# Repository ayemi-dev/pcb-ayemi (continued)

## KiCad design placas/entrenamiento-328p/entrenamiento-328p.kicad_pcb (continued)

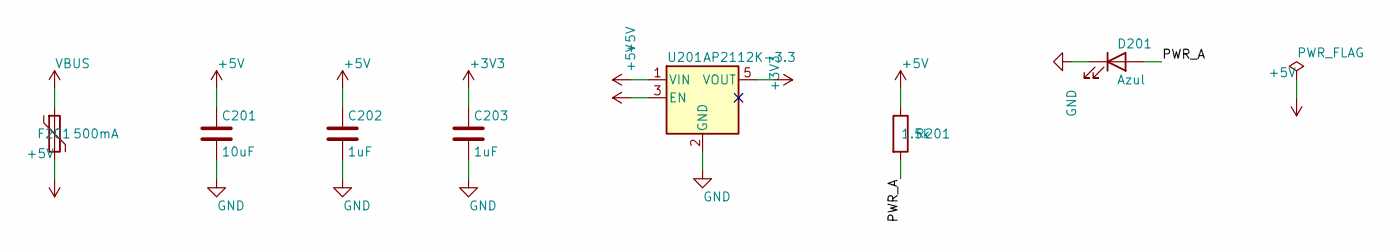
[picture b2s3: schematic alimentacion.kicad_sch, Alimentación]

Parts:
C201: 10uF; C_0603_1608Metric; LCSC C19702
C202, C203: 1uF; C_0603_1608Metric; LCSC C15849
D201: Azul; LED_0603_1608Metric; LCSC C2288
F201: 500mA; Fuse_1206_3216Metric; LCSC C163512
R201: 1.5k; R_0603_1608Metric; LCSC C22843
U201: AP2112K-3.3; SOT-23-5; LCSC C51118

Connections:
+3V3: C203.1, U201.5 (VOUT); also elsewhere on the board
+5V: C201.1, C202.1, F201.2, R201.1, U201.1 (VIN), U201.3 (EN); also elsewhere on the board
/alimentacion/PWR_A: D201.2 (A), R201.2
GND: C201.2, C202.2, C203.2, D201.1 (K), U201.2 (GND); also elsewhere on the board
VBUS: F201.1; also elsewhere on the board

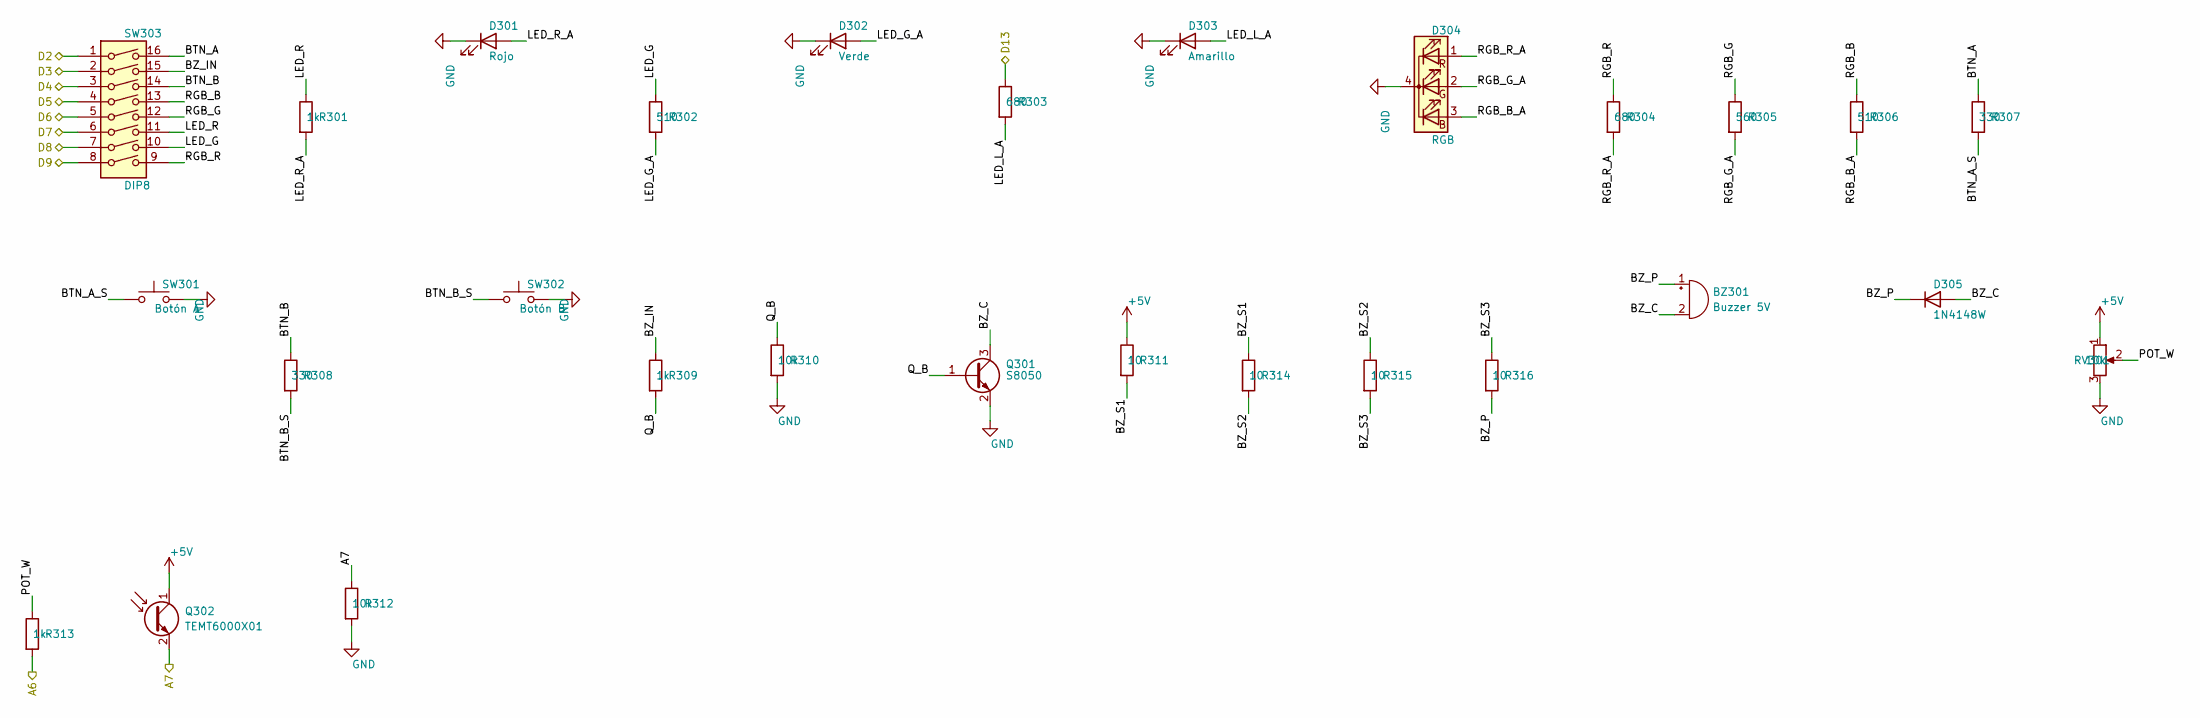
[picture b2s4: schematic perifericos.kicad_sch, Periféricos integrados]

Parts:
BZ301: Buzzer 5V; MagneticBuzzer_CUI_CMT-8504-100-SMT; LCSC C7421674
D301: Rojo; LED_0603_1608Metric; LCSC C2286
D302: Verde; LED_0603_1608Metric; LCSC C12624
D303: Amarillo; LED_0603_1608Metric; LCSC C2287
D304: RGB; LED_Avago_PLCC4_3.2x2.8mm_CW; LCSC C3647023
D305: 1N4148W; D_SOD-123; LCSC C81598
Q301: S8050; SOT-23; LCSC C2146
Q302: TEMT6000X01; LED_1206_3216Metric; LCSC C94098
R301, R309, R313: 1k; R_0603_1608Metric; LCSC C21190
R302, R306: 510; R_0603_1608Metric; LCSC C23193
R303, R304: 680; R_0603_1608Metric; LCSC C23228
R305: 560; R_0603_1608Metric; LCSC C23204
R307, R308: 330; R_0603_1608Metric; LCSC C23138
R310, R312: 10k; R_0603_1608Metric; LCSC C25804
R311, R314, R315, R316: 10; R_0603_1608Metric; LCSC C22859
RV301: 10k; Potentiometer_Alps_RK09K_Single_Vertical; LCSC C202373
SW301: Botón A; SW_Push_1TS009xxxx-xxxx-xxxx_6x6x5mm; LCSC C319409
SW302: Botón B; SW_Push_1TS009xxxx-xxxx-xxxx_6x6x5mm; LCSC C319409
SW303: DIP8; SW_DIP_SPSTx08_Slide_Omron_A6S-810x_W8.9mm_P2.54mm; LCSC C6709493

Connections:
+5V: Q302.1 (C), R311.1, RV301.1; also elsewhere on the board
/A6: R313.2; also elsewhere on the board
/A7: Q302.2 (E), R312.1; also elsewhere on the board
/D2: SW303.1; also elsewhere on the board
/D3: SW303.2; also elsewhere on the board
/D4: SW303.3; also elsewhere on the board
/D5: SW303.4; also elsewhere on the board
/D6: SW303.5; also elsewhere on the board
/D7: SW303.6; also elsewhere on the board
/D8: SW303.7; also elsewhere on the board
/D9: SW303.8; also elsewhere on the board
/D13: R303.1; also elsewhere on the board
/perifericos/BTN_A: R307.1, SW303.16
/perifericos/BTN_A_S: R307.2, SW301.1
/perifericos/BTN_B: R308.1, SW303.14
/perifericos/BTN_B_S: R308.2, SW302.1
/perifericos/BZ_C: BZ301.2 (-), D305.2 (A), Q301.3 (C)
/perifericos/BZ_IN: R309.1, SW303.15
/perifericos/BZ_P: BZ301.1 (+), D305.1 (K), R316.2
/perifericos/BZ_S1: R311.2, R314.1
/perifericos/BZ_S2: R314.2, R315.1
/perifericos/BZ_S3: R315.2, R316.1
/perifericos/LED_G: R302.1, SW303.10
/perifericos/LED_G_A: D302.2 (A), R302.2
/perifericos/LED_L_A: D303.2 (A), R303.2
/perifericos/LED_R: R301.1, SW303.11
/perifericos/LED_R_A: D301.2 (A), R301.2
/perifericos/POT_W: R313.1, RV301.2
/perifericos/Q_B: Q301.1 (B), R309.2, R310.1
/perifericos/RGB_B: R306.1, SW303.13
/perifericos/RGB_B_A: D304.3 (BA), R306.2
/perifericos/RGB_G: R305.1, SW303.12
/perifericos/RGB_G_A: D304.2 (GA), R305.2
/perifericos/RGB_R: R304.1, SW303.9
/perifericos/RGB_R_A: D304.1 (RA), R304.2
GND: D301.1 (K), D302.1 (K), D303.1 (K), D304.4 (K), Q301.2 (E), R310.2, R312.2, RV301.3, SW301.2, SW302.2; also elsewhere on the board

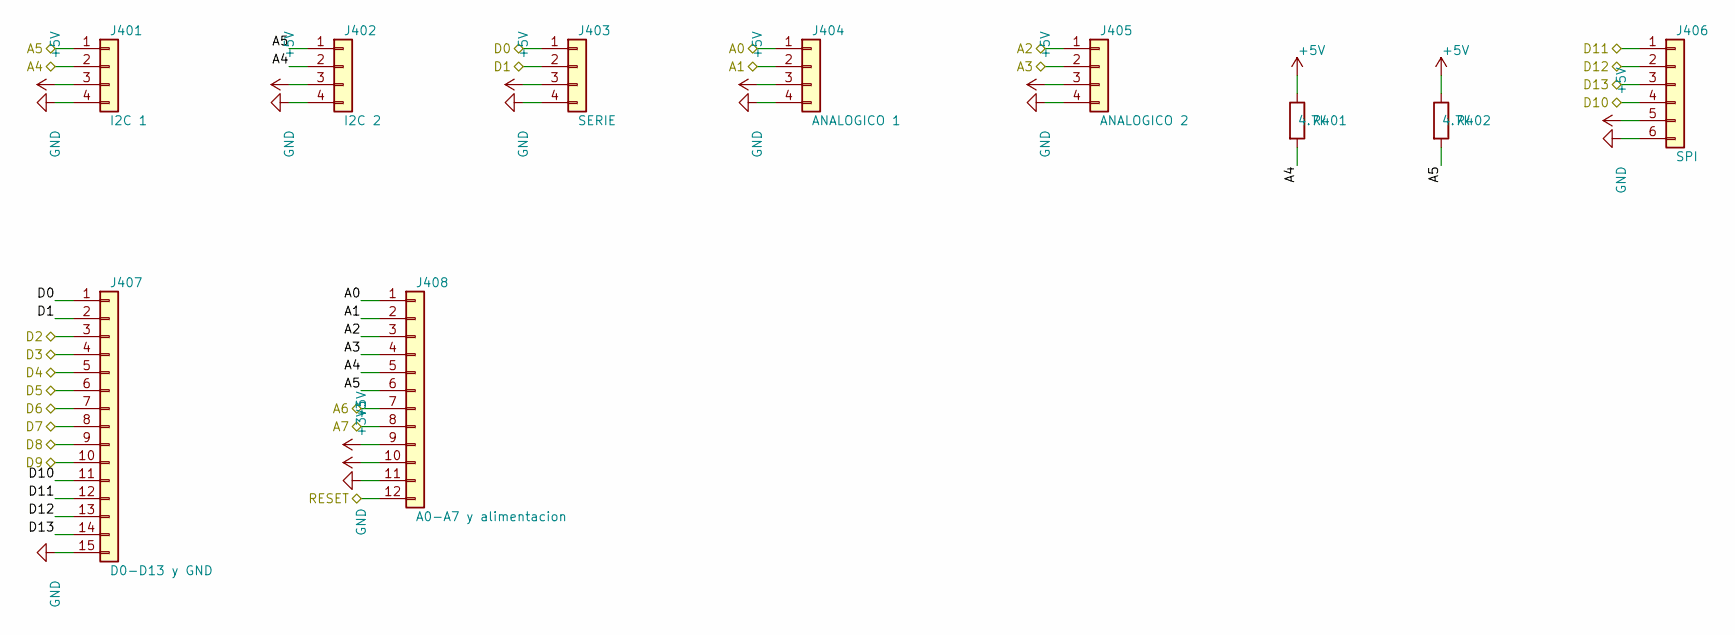
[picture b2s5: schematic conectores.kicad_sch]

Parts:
J401: I2C 1; JST_PH_S4B-PH-SM4-TB_1x04-1MP_P2.00mm_Horizontal; LCSC C265102
J402: I2C 2; JST_PH_S4B-PH-SM4-TB_1x04-1MP_P2.00mm_Horizontal; LCSC C265102
J403: SERIE; JST_PH_S4B-PH-SM4-TB_1x04-1MP_P2.00mm_Horizontal; LCSC C265102
J404: ANALOGICO 1; JST_PH_S4B-PH-SM4-TB_1x04-1MP_P2.00mm_Horizontal; LCSC C265102
J405: ANALOGICO 2; JST_PH_S4B-PH-SM4-TB_1x04-1MP_P2.00mm_Horizontal; LCSC C265102
J406: SPI; PinHeader_1x06_P2.54mm_Vertical; LCSC C492405
J407: D0-D13 y GND; PinHeader_1x15_P2.54mm_Vertical; LCSC C22465875
J408: A0-A7 y alimentacion; PinHeader_1x12_P2.54mm_Vertical; LCSC C2840012
R401, R402: 4.7k; R_0603_1608Metric; LCSC C23162

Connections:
+3V3: J408.10; also elsewhere on the board
+5V: J401.3, J402.3, J403.3, J404.3, J405.3, J406.5, J408.9, R401.1, R402.1; also elsewhere on the board
/A0: J404.1, J408.1; also elsewhere on the board
/A1: J404.2, J408.2; also elsewhere on the board
/A2: J405.1, J408.3; also elsewhere on the board
/A3: J405.2, J408.4; also elsewhere on the board
/A4: J401.2, J402.2, J408.5, R401.2; also elsewhere on the board
/A5: J401.1, J402.1, J408.6, R402.2; also elsewhere on the board
/A6: J408.7; also elsewhere on the board
/A7: J408.8; also elsewhere on the board
/D0: J403.1, J407.1; also elsewhere on the board
/D1: J403.2, J407.2; also elsewhere on the board
/D2: J407.3; also elsewhere on the board
/D3: J407.4; also elsewhere on the board
/D4: J407.5; also elsewhere on the board
/D5: J407.6; also elsewhere on the board
/D6: J407.7; also elsewhere on the board
/D7: J407.8; also elsewhere on the board
/D8: J407.9; also elsewhere on the board
/D9: J407.10; also elsewhere on the board
/D10: J406.4, J407.11; also elsewhere on the board
/D11: J406.1, J407.12; also elsewhere on the board
/D12: J406.2, J407.13; also elsewhere on the board
/D13: J406.3, J407.14; also elsewhere on the board
/RESET: J408.12; also elsewhere on the board
GND: J401.4, J402.4, J403.4, J404.4, J405.4, J406.6, J407.15, J408.11; also elsewhere on the board

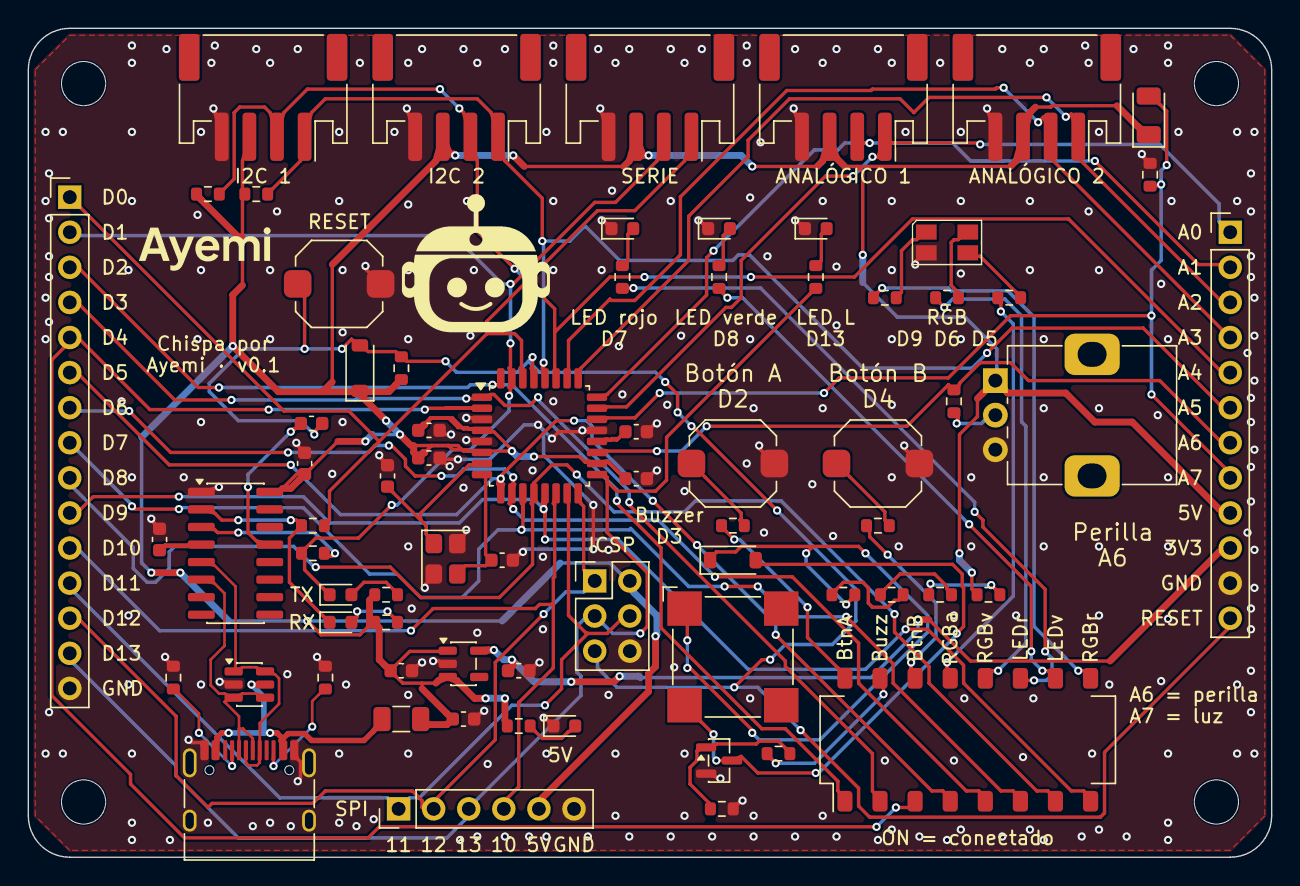
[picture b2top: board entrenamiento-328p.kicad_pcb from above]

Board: 2 copper layers, 90.0 x 60.0 mm, 75 parts (0 on the bottom side), 64 nets.

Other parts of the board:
H1, H2, H3, H4: M3; MountingHole_3.2mm_M3

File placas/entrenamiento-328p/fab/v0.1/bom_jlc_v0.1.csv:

Comment,Designator,Footprint,LCSC Part #,Clase,Alternativa
Buzzer 5V,BZ301,MagneticBuzzer_CUI_CMT-8504-100-SMT,C7421674,Extended,C530411
22pF,"C1,C2",C_0603_1608Metric,C1653,Basic,C7419421
100nF,"C3,C4,C5,C6,C101,C102,C103",C_0603_1608Metric,C14663,Basic,C91183
10uF,C201,C_0603_1608Metric,C19702,Basic,C380314
1uF,"C202,C203",C_0603_1608Metric,C15849,Basic,C106214
1N4148W,"D1,D305",D_SOD-123,C81598,Basic,C2099
C2286,"D101,D102,D301",LED_0603_1608Metric,C2286,Basic,C84263
Azul,D201,LED_0603_1608Metric,C2288,Extended,C84266
Verde,D302,LED_0603_1608Metric,C12624,Extended,C84267
Amarillo,D303,LED_0603_1608Metric,C2287,Extended,C84268
RGB,D304,LED_Avago_PLCC4_3.2x2.8mm_CW,C3647023,Extended,C601684
500mA,F201,Fuse_1206_3216Metric,C163512,Extended,C49318356
ICSP,J1,PinHeader_2x03_P2.54mm_Vertical,C65114,Extended,C53055678
USB-C,J101,USB_C_Receptacle_HRO_TYPE-C-31-M-12,C165948,Extended,C5337088
C265102,"J401,J402,J403,J404,J405",JST_PH_S4B-PH-SM4-TB_1x04-1MP_P2.00mm_Horizontal,C265102,Extended,C7429571
SPI,J406,PinHeader_1x06_P2.54mm_Vertical,C492405,Extended,C42431790
D0-D13 y GND,J407,PinHeader_1x15_P2.54mm_Vertical,C22465875,Extended,C2932704
A0-A7 y alimentacion,J408,PinHeader_1x12_P2.54mm_Vertical,C2840012,Extended,C54803345
S8050,Q301,SOT-23,C2146,Basic,C105433
TEMT6000X01,Q302,LED_1206_3216Metric,C94098,Extended,C47416518
10k,"R1,R310,R312",R_0603_1608Metric,C25804,Basic,C98220
5.1k,"R101,R102",R_0603_1608Metric,C23186,Basic,C105580
1k,"R103,R104,R301,R309,R313",R_0603_1608Metric,C21190,Basic,C22548
1.5k,"R105,R106,R201",R_0603_1608Metric,C22843,Basic,C114668
510,"R302,R306",R_0603_1608Metric,C23193,Basic,C114670
680,"R303,R304",R_0603_1608Metric,C23228,Basic,C112310
560,R305,R_0603_1608Metric,C23204,Basic,C114629
330,"R307,R308",R_0603_1608Metric,C23138,Basic,C105881
10,"R311,R314,R315,R316",R_0603_1608Metric,C22859,Basic,C109318
4.7k,"R401,R402",R_0603_1608Metric,C23162,Basic,C99782
10k,RV301,Potentiometer_Alps_RK09K_Single_Vertical,C202373,Extended,C351173
C319409,"SW1,SW301,SW302",SW_Push_1TS009xxxx-xxxx-xxxx_6x6x5mm,C319409,Extended,C255813
DIP8,SW303,SW_DIP_SPSTx08_Slide_Omron_A6S-810x_W8.9mm_P2.54mm,C6709493,Extended,C7502790
ATmega328P-AU,U1,TQFP-32_7x7mm_P0.8mm,C14877,Extended,C618816
CH340C,U101,SOIC-16_3.9x9.9mm_P1.27mm,C84681,Extended,C7464026
USBLC6-2SC6,U102,SOT-23-6,C7519,Extended,C2687116
AP2112K-3.3,U201,SOT-23-5,C51118,Extended,C82942
16MHz,Y1,Crystal_SMD_3225-4Pin_3.2x2.5mm,C70562,Extended,C362471

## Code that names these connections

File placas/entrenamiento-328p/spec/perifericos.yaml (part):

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    nota: "En ON el periférico queda conectado. HUELLA PROVISIONAL: se usa el patrón del Omron A6S (SMD, 2.54 mm, gull-wing recesado) porque el SHOU HAN lo copia; comparar con la hoja de datos antes de la fase 3."

  # ---------------- LEDs sueltos ----------------
  - {ref: R301, simbolo: "Device:R", valor: "1k", <<: *r1k, pines: {1: LED_R, 2: LED_R_A}, corriente_ma: {tipico: 2.90, maximo: 3.45}, nota: "LED rojo: (4.9 - 2.0) / 1 kΩ = 2.90 mA típico (design.md 5.4)."}
  - {ref: D301, simbolo: "Device:LED", valor: "Rojo", huella: "LED_SMD:LED_0603_1608Metric", lcsc: C2286, clase: Basic, alternativa: C84263, datasheet: "https://www.lcsc.com/datasheet/lcsc_datasheet_1810231112_Hubei-KENTO-Elec-KT-0603R_C2286.pdf", pines: {1: GND, 2: LED_R_A}}

  - {ref: R302, simbolo: "Device:R", valor: "510", <<: *r510, pines: {1: LED_G, 2: LED_G_A}, corriente_ma: {tipico: 3.53, maximo: 4.80}, nota: "LED verde de 3.1 V: (4.9 - 3.1) / 510 = 3.53 mA típico."}
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
  - {ref: R303, simbolo: "Device:R", valor: "680", <<: *r680, pines: {1: D13, 2: LED_L_A}, corriente_ma: {tipico: 3.68, maximo: 4.78}, nota: "LED amarillo «L» en D13 (sin DIP): (4.9 - 2.4) / 680 = 3.68 mA típico."}
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
  # ---------------- LED RGB de cátodo común ----------------
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    alternativa: C601684
    justificacion: "RGB de cátodo común 3528: no hay Basic."
    datasheet: "https://wmsc.lcsc.com/wmsc/upload/file/pdf/v2/lcsc/2207041845_XINGLIGHT-XL-A3528RGBC-BM_C3647023.pdf"
    pines: {1: RGB_R_A, 2: RGB_G_A, 3: RGB_B_A, 4: GND}
    nota: "HUELLA PROVISIONAL: el orden de pines del XL-A3528RGBC-BM y el pin 1 se comparan con su hoja de datos antes de la fase 3. La alternativa C601684 es de 1.6x1.5 mm (otra huella)."
  - {ref: R304, simbolo: "Device:R", valor: "680", <<: *r680, pines: {1: RGB_R, 2: RGB_R_A}, corriente_ma: {tipico: 4.26, maximo: 5.07}, nota: "RGB rojo: (4.9 - 2.0) / 680 = 4.26 mA típico; máximo 5.07 mA (excepción aceptada, design.md 5.4)."}
  - {ref: R305, simbolo: "Device:R", valor: "560", <<: *r560, pines: {1: RGB_G, 2: RGB_G_A}, corriente_ma: {tipico: 3.39, maximo: 4.38}, nota: "RGB verde: (4.9 - 3.0) / 560 = 3.39 mA típico."}
  - {ref: R306, simbolo: "Device:R", valor: "510", <<: *r510, pines: {1: RGB_B, 2: RGB_B_A}, corriente_ma: {tipico: 3.73, maximo: 4.80}, nota: "RGB azul: (4.9 - 3.0) / 510 = 3.73 mA típico."}

  # ---------------- Botones A y B ----------------
  - {ref: R307, simbolo: "Device:R", valor: "330", <<: *r330, pines: {1: BTN_A, 2: BTN_A_S}, corriente_ma: {tipico: 0.14, maximo: 0.26}, nota: "Protección del pin: 5.25 V / 330 Ω = 15.9 mA si el código lo pone en salida alta."}
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  - {ref: R308, simbolo: "Device:R", valor: "330", <<: *r330, pines: {1: BTN_B, 2: BTN_B_S}, corriente_ma: {tipico: 0.14, maximo: 0.26}, nota: "Igual que R307."}
  - {ref: SW302, simbolo: "Switch:SW_Push", valor: "Botón B", huella: "Button_Switch_SMD:SW_Push_1TS009xxxx-xxxx-xxxx_6x6x5mm", <<: *tact, pines: {1: BTN_B_S, 2: GND}, nota: "Igual que SW301."}

  # ---------------- Buzzer pasivo magnético con transistor ----------------
  - {ref: R309, simbolo: "Device:R", valor: "1k", <<: *r1k, pines: {1: BZ_IN, 2: Q_B}, nota: "Base de Q301: Ib = (4.5 - 0.8) / 1 kΩ - 0.08 mA = 3.6 mA; beta forzada = 76 / 3.6 = 21 (hFE mínimo 200)."}
  - {ref: R310, simbolo: "Device:R", valor: "10k", <<: *r10k, pines: {1: Q_B, 2: GND}, nota: "Mantiene la base en bajo con el DIP en OFF o los pines en alta impedancia."}
  - ref: Q301
    simbolo: "Transistor_BJT:MMBT3904"
    valor: "S8050"
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    clase: Basic
    alternativa: C105433
    datasheet: "https://www.lcsc.com/datasheet/lcsc_datasheet_2310131500_Jiangsu-Changjing-Electronics-Technology-Co---Ltd--S8050-J3Y-RANGE-200-350_C2146.pdf"
    pines: {1: Q_B, 2: GND, 3: BZ_C}
    nota: "Se usa el símbolo del MMBT3904 porque comparte el orden de pines del SOT-23 (1 B, 2 E, 3 C). Confirmar el pinout del S8050 J3Y en la hoja de datos (tarea 2.9)."
  - {ref: R311, simbolo: "Device:R", valor: "10", <<: *r10, pines: {1: "+5V", 2: BZ_S1}, nota: "Serie del buzzer: 4 x 10 Ω = 40 Ω. I = 5.05 / (40 + 26...34) = 76 a 68 mA; P = 58 mW por resistencia (design.md 5.4)."}
  - {ref: R314, simbolo: "Device:R", valor: "10", <<: *r10, pines: {1: BZ_S1, 2: BZ_S2}, nota: "Serie del buzzer (2 de 4)."}
  - {ref: R315, simbolo: "Device:R", valor: "10", <<: *r10, pines: {1: BZ_S2, 2: BZ_S3}, nota: "Serie del buzzer (3 de 4)."}
  - {ref: R316, simbolo: "Device:R", valor: "10", <<: *r10, pines: {1: BZ_S3, 2: BZ_P}, nota: "Serie del buzzer (4 de 4)."}
  - ref: BZ301
    simbolo: "Device:Buzzer"
    valor: "Buzzer 5V"
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    justificacion: "Zumbador pasivo electromagnético de 5 V SMD: ninguno es Basic."
    datasheet: "https://wmsc.lcsc.com/wmsc/upload/file/pdf/v2/lcsc/2306141737_Fengming-YS-SBZ8530C05R30_C7421674.pdf"
    corriente_ma: {tipico: 68.6, maximo: 76.5}
    pines: {1: BZ_P, 2: BZ_C}
    nota: "Bobina de unos 30 +/- 4 ohm (dato de una hoja genérica de 8530 de 5 V; confirmar con la del Fengming, tarea 2.9). HUELLA PROVISIONAL: la CUI CMT-8504 es de 8.5 mm; comparar con la hoja de datos antes de la fase 3."
  - {ref: D305, simbolo: "Diode:1N4148W", valor: "1N4148W", huella: "Diode_SMD:D_SOD-123", <<: *d4148, pines: {1: BZ_P, 2: BZ_C}, nota: "Diodo de protección de la bobina (cátodo en BZ_P)."}

  # ---------------- Potenciómetro (A6) ----------------
  - ref: RV301
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    justificacion: "Potenciómetro rotativo de 10 kΩ: ninguno es Basic. La perilla se compra aparte."
    datasheet: "https://www.lcsc.com/datasheet/lcsc_datasheet_1810170725_ALPSALPINE-RK09K1130AAU_C202373.pdf"
    corriente_ma: {tipico: 0.50, maximo: 0.525}
    pines: {1: "+5V", 2: POT_W, 3: GND}
    nota: "Confirmar en la hoja de datos que el taper es lineal (B) y la corriente máxima del cursor."
  - {ref: R313, simbolo: "Device:R", valor: "1k", <<: *r1k, pines: {1: POT_W, 2: A6}, nota: "Protege el cursor de un corto desde el header: 5.25 mA máximo. Impedancia de fuente al ADC <= 3.5 kΩ."}

  # ---------------- Sensor de luz (A7) ----------------
  - ref: Q302
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
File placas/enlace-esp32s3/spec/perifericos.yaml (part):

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  C: "Capacitor_SMD:C_0603_1608Metric"
componentes:
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  - {ref: R301, simbolo: "Device:R", valor: "330", lcsc: C23138, clase: Basic, alternativa: C105881, datasheet: "https://www.lcsc.com/product-detail/C23138.html", pines: {1: LED_R, 2: LED_R_A}, nota: "LED rojo (Vf 1.7 a 1.9 V a 5 mA, hoja de KT-0603-R): (3.2 - 1.8) / 330 = 4.2 mA."}
  - {ref: D301, simbolo: "Device:LED", valor: "Rojo", huella: "LED_SMD:LED_0603_1608Metric", lcsc: C2286, clase: Basic, alternativa: C84263, datasheet: "https://www.lcsc.com/product-detail/C2286.html", pines: {1: GND, 2: LED_R_A}}
  - {ref: R302, simbolo: "Device:R", valor: "330", lcsc: C23138, clase: Basic, alternativa: C105881, datasheet: "https://www.lcsc.com/product-detail/C23138.html", pines: {1: LED_G, 2: LED_G_A}, nota: "LED verde amarillento (Vf 2.0 a 2.2 V a 20 mA según JLCPCB): (3.2 - 2.1) / 330 = 3.3 mA."}
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  - {ref: R303, simbolo: "Device:R", valor: "330", lcsc: C23138, clase: Basic, alternativa: C105881, datasheet: "https://www.lcsc.com/product-detail/C23138.html", pines: {1: LED_Y, 2: LED_Y_A}, nota: "LED amarillo (Vf 1.9 a 2.3 V a 20 mA, hoja de KT-0603-Y): (3.2 - 2.0) / 330 = 3.6 mA."}
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  - {ref: R320, simbolo: "Device:R", valor: "10k", lcsc: C25804, clase: Basic, alternativa: C98220, datasheet: "https://www.lcsc.com/product-detail/C25804.html", pines: {1: RGB_R, 2: GND}, nota: "Mantiene la compuerta en bajo con el DIP en OFF."}
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  - {ref: R321, simbolo: "Device:R", valor: "10k", lcsc: C25804, clase: Basic, alternativa: C98220, datasheet: "https://www.lcsc.com/product-detail/C25804.html", pines: {1: RGB_G, 2: GND}, nota: "Mantiene la compuerta en bajo con el DIP en OFF."}
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  - {ref: R322, simbolo: "Device:R", valor: "10k", lcsc: C25804, clase: Basic, alternativa: C98220, datasheet: "https://www.lcsc.com/product-detail/C25804.html", pines: {1: RGB_B, 2: GND}, nota: "Mantiene la compuerta en bajo con el DIP en OFF."}
  - {ref: R307, simbolo: "Device:R", valor: "330", lcsc: C23138, clase: Basic, alternativa: C105881, datasheet: "https://www.lcsc.com/product-detail/C23138.html", pines: {1: BTN_A, 2: BTN_A_S}, nota: "Protección del pin."}
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  - {ref: R308, simbolo: "Device:R", valor: "330", lcsc: C23138, clase: Basic, alternativa: C105881, datasheet: "https://www.lcsc.com/product-detail/C23138.html", pines: {1: BTN_B, 2: BTN_B_S}, nota: "Igual que R307."}
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  - {ref: R310, simbolo: "Device:R", valor: "10k", lcsc: C25804, clase: Basic, alternativa: C98220, datasheet: "https://www.lcsc.com/product-detail/C25804.html", pines: {1: Q_B, 2: GND}, nota: "Mantiene la base en bajo con el DIP en OFF."}
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  - {ref: R311, simbolo: "Device:R", valor: "10", lcsc: C22859, clase: Basic, alternativa: C109318, datasheet: "https://www.lcsc.com/product-detail/C22859.html", pines: {1: "+5V", 2: BZ_S1}, nota: "Serie del buzzer: 4 x 10 Ω = 40 Ω."}
  - {ref: R314, simbolo: "Device:R", valor: "10", lcsc: C22859, clase: Basic, alternativa: C109318, datasheet: "https://www.lcsc.com/product-detail/C22859.html", pines: {1: BZ_S1, 2: BZ_S2}}
  - {ref: R315, simbolo: "Device:R", valor: "10", lcsc: C22859, clase: Basic, alternativa: C109318, datasheet: "https://www.lcsc.com/product-detail/C22859.html", pines: {1: BZ_S2, 2: BZ_S3}}
  - {ref: R316, simbolo: "Device:R", valor: "10", lcsc: C22859, clase: Basic, alternativa: C109318, datasheet: "https://www.lcsc.com/product-detail/C22859.html", pines: {1: BZ_S3, 2: BZ_P}}
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  - {ref: D305, simbolo: "Diode:1N4148W", valor: "1N4148W", huella: "Diode_SMD:D_SOD-123", lcsc: C81598, clase: Basic, alternativa: C2099, datasheet: "https://www.lcsc.com/product-detail/C81598.html", pines: {1: BZ_P, 2: BZ_C}, nota: "Diodo de protección de la bobina."}
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  - {ref: R313, simbolo: "Device:R", valor: "1k", lcsc: C21190, clase: Basic, alternativa: C22548, datasheet: "https://www.lcsc.com/product-detail/C21190.html", pines: {1: POT_W, 2: IO1}, nota: "Protege el cursor de un corto desde el header: 3.3 mA máximo."}
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  - {ref: R312, simbolo: "Device:R", valor: "10k", lcsc: C25804, clase: Basic, alternativa: C98220, datasheet: "https://www.lcsc.com/product-detail/C25804.html", pines: {1: IO2, 2: GND}}
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
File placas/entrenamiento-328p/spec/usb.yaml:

# Hoja «usb»: USB-C, protección ESD, CH340C, líneas serie, LEDs TX/RX y autorreset.
# Cálculos: design.md 5.2.
meta:
  hoja: usb.kicad_sch
  titulo: "USB y serie"
  referencias: [101, 199]

redes_de_poder: ["VBUS", "+5V", "GND"]

etiquetas_jerarquicas:
  - {red: D0,    forma: bidirectional}
  - {red: D1,    forma: bidirectional}
  - {red: RESET, forma: bidirectional}

por_defecto:
  R: "Resistor_SMD:R_0603_1608Metric"
  C: "Capacitor_SMD:C_0603_1608Metric"

piezas:
  r5k1: &r5k1 {lcsc: C23186, clase: Basic, alternativa: C105580, datasheet: "https://www.lcsc.com/datasheet/lcsc_datasheet_2206010116_UNI-ROYAL-Uniroyal-Elec-0603WAF5101T5E_C23186.pdf"}
  r1k: &r1k {lcsc: C21190, clase: Basic, alternativa: C22548, datasheet: "https://www.lcsc.com/datasheet/lcsc_datasheet_2206010130_UNI-ROYAL-Uniroyal-Elec-0603WAF1001T5E_C21190.pdf"}
  r1k5: &r1k5 {lcsc: C22843, clase: Basic, alternativa: C114668, datasheet: "https://www.lcsc.com/datasheet/lcsc_datasheet_2206010130_UNI-ROYAL-Uniroyal-Elec-0603WAF1501T5E_C22843.pdf"}
  c100n: &c100n {lcsc: C14663, clase: Basic, alternativa: C91183, datasheet: "https://www.lcsc.com/datasheet/lcsc_datasheet_2211101700_YAGEO-CC0603KRX7R9BB104_C14663.pdf"}
  led_rojo: &led_rojo {lcsc: C2286, clase: Basic, alternativa: C84263, datasheet: "https://www.lcsc.com/datasheet/lcsc_datasheet_1810231112_Hubei-KENTO-Elec-KT-0603R_C2286.pdf"}

componentes:
  - ref: J101
    simbolo: "Connector:USB_C_Receptacle_USB2.0_16P"
    valor: "USB-C"
    huella: "Connector_USB:USB_C_Receptacle_HRO_TYPE-C-31-M-12"
    lcsc: C165948
    clase: Extended
    alternativa: C5337088
    justificacion: "Receptáculo USB-C de 16 pines: ninguno es Basic (consulta 2026-10-28)."
    datasheet: "https://www.lcsc.com/datasheet/lcsc_datasheet_2205251630_Korean-Hroparts-Elec-TYPE-C-31-M-12_C165948.pdf"
    pines:
      A1: GND
      A4: VBUS
      A5: CC1
      A6: USB_DP
      A7: USB_DM
      A8: NC          # SBU1
      A9: VBUS
      A12: GND
      B1: GND
      B4: VBUS
      B5: CC2
      B6: USB_DP
      B7: USB_DM
      B8: NC          # SBU2
      B9: VBUS
      B12: GND
      SH: GND
    nota: "Solo 5 V y datos. CC1 y CC2 con 5.1 kΩ a GND (R101, R102)."

  - {ref: R101, simbolo: "Device:R", valor: "5.1k", <<: *r5k1, pines: {1: CC1, 2: GND}, nota: "Rd de CC1: 5.1 kΩ (USB-C pide 5.1 kΩ ±20 %); sin ella el cargador no da 5 V."}
  - {ref: R102, simbolo: "Device:R", valor: "5.1k", <<: *r5k1, pines: {1: CC2, 2: GND}, nota: "Rd de CC2: 5.1 kΩ."}

  - ref: U102
    simbolo: "Power_Protection:USBLC6-2SC6"
    valor: "USBLC6-2SC6"
    huella: "Package_TO_SOT_SMD:SOT-23-6"
    lcsc: C7519
    clase: Extended
    alternativa: C2687116
    justificacion: "Arreglo TVS de USB en SOT-23-6: no hay Basic."
    datasheet: "https://www.lcsc.com/datasheet/lcsc_datasheet_2410121836_STMicroelectronics-USBLC6-2SC6_C7519.pdf"
    pines: {1: USB_DP, 2: GND, 3: USB_DM, 4: USB_DM, 5: VBUS, 6: USB_DP}
    nota: "En línea: pines 1 y 6 son D+ y 3 y 4 son D-. A menos de 5 mm del conector (requisito 2.6)."

  - ref: U101
    simbolo: "Interface_USB:CH340C"
    valor: "CH340C"
    huella: "Package_SO:SOIC-16_3.9x9.9mm_P1.27mm"
    lcsc: C84681
    clase: Extended
    alternativa: C7464026
    justificacion: "Convertidor USB-serie con oscilador interno: ninguna variante CH340 es Basic. JLCPCB lo marca como descontinuado; plan B en reportes/piezas.md."
    datasheet: "https://www.lcsc.com/datasheet/lcsc_datasheet_2406191656_WCH-Jiangsu-Qin-Heng-CH340C_C84681.pdf"
    corriente_ma: {tipico: 10, maximo: 15}
    pines:
      1: GND
      2: CH_TXD
      3: CH_RXD
      4: V3
      5: USB_DP
      6: USB_DM
      7: NC
      8: NC
      9: NC       # CTS
      10: NC      # DSR
      11: NC      # RI
      12: NC      # DCD
      13: DTR
      14: NC      # RTS
      15: NC      # R232: se confirma con la hoja de datos (tarea 2.9)
      16: "+5V"
    nota: "Corriente de 10/15 mA estimada. V3 lleva 100 nF a GND (C102) con alimentación de 5 V."

  - {ref: C101, simbolo: "Device:C", valor: "100nF", <<: *c100n, pines: {1: "+5V", 2: GND}, nota: "Desacoplo de VCC del CH340C."}
  - {ref: C102, simbolo: "Device:C", valor: "100nF", <<: *c100n, pines: {1: V3, 2: GND}, nota: "Condensador de V3 (fuente interna) a 5 V."}
  - {ref: C103, simbolo: "Device:C", valor: "100nF", <<: *c100n, pines: {1: DTR, 2: RESET}, nota: "Autorreset: DTR# a RESET por 100 nF. tau = 10 kΩ x 100 nF = 1 ms; RESET queda 105 µs bajo VIL."}

  - {ref: R103, simbolo: "Device:R", valor: "1k", <<: *r1k, pines: {1: CH_TXD, 2: D0}, nota: "Serie TXD del CH340 hacia D0 (RX del micro): 1 kΩ."}
  - {ref: R104, simbolo: "Device:R", valor: "1k", <<: *r1k, pines: {1: D1, 2: CH_RXD}, nota: "Serie D1 (TX del micro) hacia RXD del CH340: 1 kΩ."}

  - ref: D101
    simbolo: "Device:LED"
    valor: "TX"
    huella: "LED_SMD:LED_0603_1608Metric"
    <<: *led_rojo
    pines: {1: D1, 2: TX_A}
    nota: "LED de TX en la red D1; enciende cuando D1 baja."
  - {ref: R105, simbolo: "Device:R", valor: "1.5k", <<: *r1k5, pines: {1: "+5V", 2: TX_A}, corriente_ma: {tipico: 1.87, maximo: 2.23}, nota: "I = (5.0 - 2.0 - 0.2) / 1.5 kΩ = 1.87 mA típico; 2.23 mA máximo (design.md 5.2)."}

  - ref: D102
    simbolo: "Device:LED"
    valor: "RX"
    huella: "LED_SMD:LED_0603_1608Metric"
    <<: *led_rojo
    pines: {1: CH_TXD, 2: RX_A}
    nota: "LED de RX en TXD del CH340 (antes de R103); enciende cuando la línea baja."
  - {ref: R106, simbolo: "Device:R", valor: "1.5k", <<: *r1k5, pines: {1: "+5V", 2: RX_A}, corriente_ma: {tipico: 1.87, maximo: 2.23}, nota: "Igual que R105."}

  - {ref: "#FLG01", simbolo: "power:PWR_FLAG", valor: "PWR_FLAG", pines: {1: VBUS}, bom: false, nota: "VBUS nace en el conector."}
  - {ref: "#FLG02", simbolo: "power:PWR_FLAG", valor: "PWR_FLAG", pines: {1: GND}, bom: false, nota: "GND nace en el conector."}
